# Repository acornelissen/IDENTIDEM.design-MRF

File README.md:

# IDENTIDEM.design M(edium Format) (R)ange(F)inder

**Before anything else, a big thank you to Oscar from Panomicron for making the CAD files for his [Thulium 6x9](https://www.panomicron.com/thulium) available for download. This camera is a heavily modified version of the Thulium, and wouldn't exist if it wasn't for Oscar's excellent work.**

_[MRF2 has dropped!](https://github.com/acornelissen/IDENTIDEM.design-MRF2) It's a more involved, slightly more complex build, but has improvements all around._

My goal for this camera was to build _my_ ideal medium format rangefinder using what I learned from designing and building the LRF45, with no limits on complexity, cost, and time. As I kept working on it, it evolved and evolved, and I think I've finally reached that goal.

The detailed build guide should drop soon(ish). For now though, everything you need to build one of your own modern medium format rangefinders is in this repository.

## Features
- Uses "LiDAR" to measure distance to subject (not true LiDAR, but a ToF sensor that uses a focused IR LED array) 
- Can be used with any Mamiya Universal Press lens and couples to the original lens rangefinder mechanism with a high-precision linear position sensor
- This means that the lens position and distance measured is electronically coupled, making this the first multi-lens, electronically coupled rangefinder that I know of
- In addition, there is an intuitive in-camera lens calibration routine to make sure your camera and lens work together perfectly
- Multi-format, with masks for 6x7, 6x6, 6x4.5 and 35mm Panoramics
- Uses a high-precision rotary encoder coupled to the take-up spool to count revolutions, which is then used to accurately count frames regardless of selected format
- Built-in lightmeter
- Built-in accelerometer / gyro
- In-viewfinder OLED display with:
  - Lightmeter information: Selected ISO, selected aperture, and calculated shutter speed
  - Lens focus distance
  - Distance to subject
  - Frame lines that adjust according to selected lens
  - Masking that adjusts to selected format
  - Reticle for focus that indicates focus accuracy as lens focus distance and distance to subject converges
  - Horizon indicator
- External OLED display with:
  - Frame counter
  - Battery life percentage
  - Selected format
  - Selected lens
- Open source! 

## Bill of Materials
See the Build Guide PDF for the BoM. 

---
🍺 <strong><a href="https://paypal.me/albertcor">Buy me a beer</a></strong> if you'd like to say thank you.

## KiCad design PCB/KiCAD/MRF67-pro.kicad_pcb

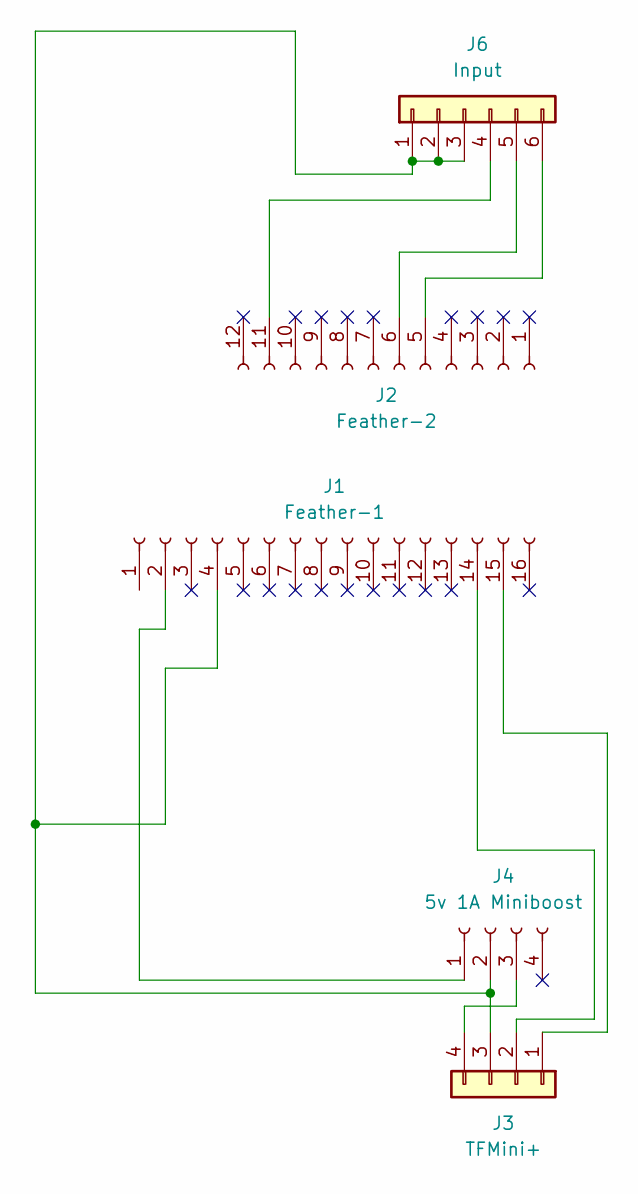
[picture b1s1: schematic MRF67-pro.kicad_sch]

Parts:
J1: Feather-1; PinHeader_1x16_P2.54mm_Vertical
J2: Feather-2; PinHeader_1x12_P2.54mm_Vertical
J3: TFMini+; JST_XH_B4B-XH-A_1x04_P2.50mm_Vertical
J4: 5v 1A Miniboost; PinHeader_1x04_P2.54mm_Vertical
J6: Input; JST_XH_B6B-XH-AM_1x06_P2.50mm_Vertical

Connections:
unnamed: J1.2, J4.1
unnamed: J1.4, J3.3, J4.2, J6.1, J6.2, J6.3
unnamed: J1.14, J3.2
unnamed: J1.15, J3.1
unnamed: J2.5, J6.6
unnamed: J2.6, J6.5
unnamed: J2.11, J6.4
unnamed: J3.4, J4.3

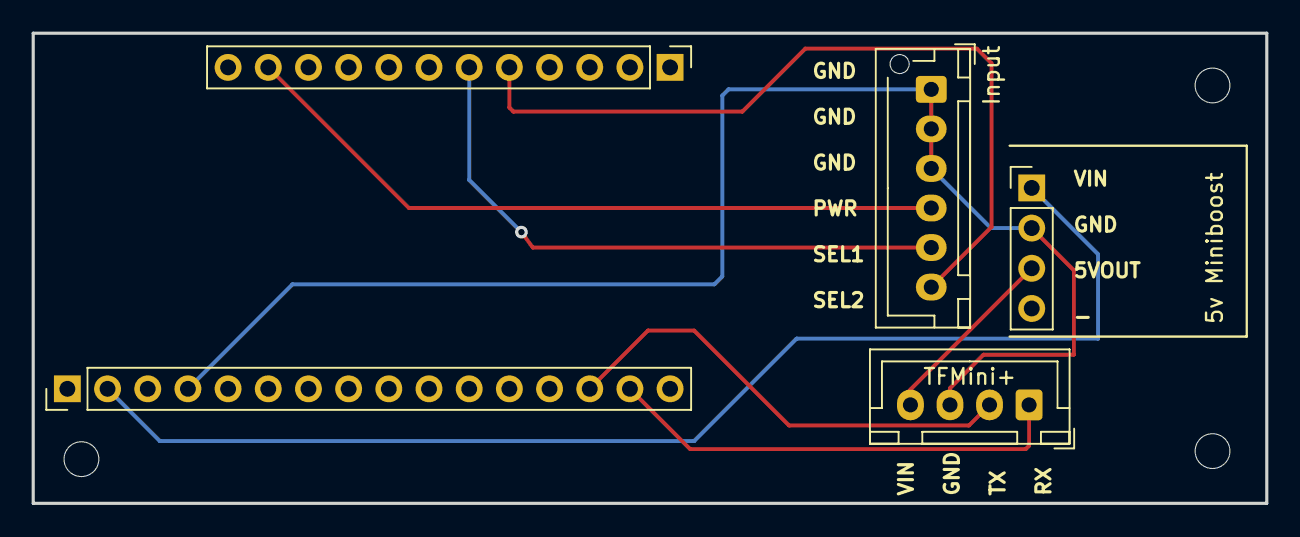
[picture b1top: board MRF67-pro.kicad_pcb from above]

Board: 2 copper layers, 78.0 x 29.7 mm, 5 parts (0 on the bottom side), 8 nets.

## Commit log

2024-04-09 Initial commut
2024-04-09 Update gitignore
2024-04-10 unnecessary
2024-04-10 Reset LiDAR on startup and set frame rate to 20HZ.
2024-04-10 Remove unused variables.
2024-04-10 Fix formatting and tab spacing.
2024-04-10 remove duplicate call to drawExternalUI
2024-04-14 Start cleaning up the structure. Still need to organise things into classes.
2024-04-19 Replace 128x64 SSD1306 with SH1107 128x128 OLED - and cheap rotary encoder breakout with Adafruit STEMMA I2C Seesaw Rotary Encoder breakout.
2024-04-20 Improvements
    - Tie framelines to lens and film format
    - Fix setting encoder value
    - Reduce smoothing window size to speed up lens distance feedback
    - General UI improvements for bigger viewfinder
2024-04-22 Even more improvements and updating of defaults
    - All lenses now have their own correct framelines, except for 55mm and 65mm which are identical, because my VF optics don't cover 55mm
    - Masking for formats now shrink to the relevant frame lines
    - We have a Neopixel RGB LED on the rotary encoder breakout board, so might as well use it
    - Add a LIDAR_OFFSET constant and apply it to the distance measured
2024-04-29 Start counting frames two clicks earlier.
2024-05-01 We now use an external ADC instead of the ESP32's noisy internal ADC
    Also update hardware info in readme to be more precise and include links.
2024-05-02 Add in MPU support to display horizon levels in UI.
    This thing is just getting more and more complex, isn't it? Well, my photos had wonky horizons and we'll have none of that.
2024-05-02 Cleanup and usability improvements.
2024-05-03 Add PCB, STEP and 3MF files, and re-organize things a bit.
2024-05-03 Call things what they are, not what copilot thinks they are.
2024-05-03 Create LICENSE
2024-05-16 Add build guide and Orcaslicer files.
2024-05-17 Add three rotations of the take up spool for each 120 format to make sure we get a whole first frame.
2024-05-17 Chane typo for beam splitter width from 1.2mm to 1.1mm
2024-05-17 Sorted LiDAR readings.
2024-05-18 Add firmware flashing guide.
2024-05-24 Add sleepmode and snap frame count.
2024-05-24 Improve device sleep mode and frame counter snapping.
2024-05-24 Add sleep mode section to manual.
2024-05-27 If there are no saved settings, don't try to load any.
2024-05-27 Modify advance plate to not fit so snug
2024-05-27 Update plate in step file as well.
2024-05-28 Add note / section about power management and buttons.
2024-05-28 add initial deepsleep code
2024-05-29 A buncha buncha power-saving changes.
    - Disable WiFI and BT on startup - not being used at the moment.
    - Implement proper deep sleep: (L) button for 5 seconds "turns off" the camera, (R) for 5 seconds then "turns it back on" again.
2024-05-29 Remove unused code.
2024-05-29 toggle lidar for deep sleep as well
2024-05-30 A few updates
    - Put deepsleep behind a toggle constant
    - make sure all button presses update last activity time
    - advance knob rotary encoder now also brings camera out of "light sleep"
    - bring back bootup screen on first start
2024-06-01 Update a few parts, specifically a new mount for the better switch. Also update build guide.
2024-06-04 Increased wall thicknesses and changed a few bits for MJF printing.
    The previous lens cone and film door were not 100% light tight when printed with MJF (or at least the ones I had printed by JLCPCB were not), which would fog the current frame in bright sunlight over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
    Added some extra support to the LiDAR mount.
    Added an extra channel for routing wire below the viewfinder.
2024-06-05 Porting dfrobot_firebeetle2_esp32s3
2024-06-09 Update lenscone mount diameter.
2024-06-10 More updates to lens mount diameters.
2024-06-21 Fix for issue #10
    https://github.com/acornelissen/IDENTIDEM.design-MRF/issues/10
2024-06-21 Add 6x9 sensor values, commented, for a future version of the camera.
2024-06-22 Some small tweaks from user feedback. Thanks Mason!
2024-08-02 Fix some typos and apply calibrated reticle position.
2024-08-07 Interface tweaks.
2024-08-29 Changes for latest version of camera.
2024-09-11 Changes for Instax MRF
2024-09-15 PEC11 has been discontinued, update build guide with alternative, PEC11R.
2024-10-11 Much better lens sensor readings and a few other tweaks.
2024-10-17 tweaks
2024-10-18 Let's gooooo.
2024-10-18 Update sleedmode ui to use internal display.
2024-10-18 Interface updates.
2024-10-21 Work
2024-10-22 Put back loadprefs.
2024-10-24 More tweaks.
2024-10-24 Properly soldered encoders will not read a negative value - fix this in the code.
2024-10-28 Update sensor values for frames.
2024-11-05 Take out of sleepmode first on film adavance.
2024-11-07 Better handling of lidar status in sleep mode.
2024-11-07 Better handling of lidar status.
2024-11-07 updates to constants
2024-11-10 More changes. Lidar offset perfect now, display a little more accurate.
2024-11-12 Update frame sensor counts.
2024-11-26 Adding roll end film counter logic and moving a few calls out of an if statement in an attempt to reduce the offset between lens sensor readings.
2024-12-18 Add parallax offset in the interface. A few other tweaks too.
2024-12-30 More accurate frame spacing.
    Bringing over the frame spacing sensor values from v2, which were calculated with help from Oscar Oweson's spool maths spreadsheet.
2025-05-01 Big refactor - still to flash and test.
2025-05-06 Properly organise project. Remove unused deepsleep code.
2025-05-12 A few small fixes. v7 is go!
2025-11-18 Update README with MRF2 release information
    Added a note about MRF2 release and its improvements.
